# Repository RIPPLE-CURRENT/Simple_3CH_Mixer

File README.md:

# Simple_3CH_Mixer

Simple 3 Channel Eurorack synth Mixer

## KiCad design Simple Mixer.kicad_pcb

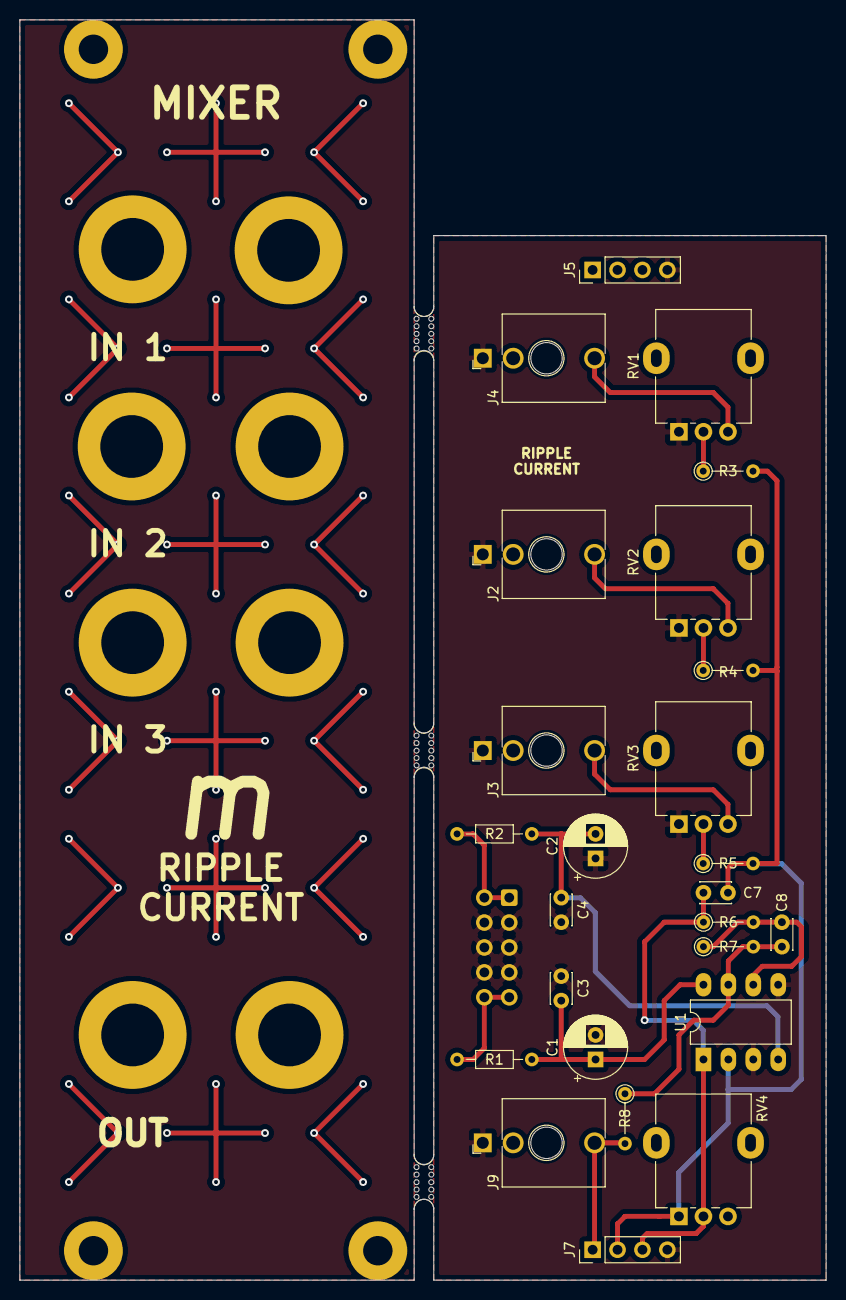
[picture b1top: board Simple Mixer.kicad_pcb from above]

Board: 2 copper layers, 82.2 x 128.5 mm, 29 parts (1 on the bottom side), 16 nets.

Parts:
C1, C2: 10u; CP_Radial_D6.3mm_P2.50mm
C3, C4: 100n; C_Disc_D3.0mm_W2.0mm_P2.50mm
C7, C8: 47pF; C_Disc_D3.0mm_W2.0mm_P2.50mm
J1: POWER INPUT; IDC-Header_2x05_P2.54mm_Vertical
J2: IN2; Jack_3.5mm_QingPu_WQP-PJ398SM_Vertical_CircularHoles
J3: IN3; Jack_3.5mm_QingPu_WQP-PJ398SM_Vertical_CircularHoles
J4: IN1; Jack_3.5mm_QingPu_WQP-PJ398SM_Vertical_CircularHoles
J5, J7: PCB JUMPER; PinHeader_1x04_P2.54mm_Vertical
J9: OUT; Jack_3.5mm_QingPu_WQP-PJ398SM_Vertical_CircularHoles
R1, R2: FERRITE; R_Axial_DIN0204_L3.6mm_D1.6mm_P7.62mm_Horizontal
R3, R4, R5, R6, R7: 100k; R_Axial_DIN0204_L3.6mm_D1.6mm_P5.08mm_Vertical
R8: 330; R_Axial_DIN0204_L3.6mm_D1.6mm_P5.08mm_Vertical
RV1, RV2, RV3, RV4: 100K; Potentiometer_Alpha_RD901F-40-00D_Single_Vertical
U1: TL072; DIP-8_W7.62mm_LongPads
mouse-bite-3mm-slot, mouse-bite-3mm-slot#2, mouse-bite-3mm-slot#3: VAL**; mouse-bite-3mm-slot

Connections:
+12V: C1.1, C3.2, R1.1, U1.8
-12V: C2.2, C4.1, R2.1, U1.4
GND: C1.2, C2.1, C3.1, C4.2, J1.3, J1.4, J1.5, J1.6, J1.7, J1.8, J2.G, J3.G, J4.G, J5.4, J7.4, J9.G, RV1.1, RV2.1, RV3.1, U1.3, U1.5
IN1: C7.2, J7.2, R3.2, R4.2, R5.2, RV4.1, U1.2
unnamed: C8.1, R7.2, R8.1, U1.7
unnamed: C8.2, R6.2, R7.1, U1.6
unnamed: J1.1, J1.2, R2.2
unnamed: J1.9, J1.10, R1.2
unnamed: J2.T, RV2.3
unnamed: J3.T, RV3.3
unnamed: J4.T, RV1.3
unnamed: R3.1, RV1.2
unnamed: R4.1, RV2.2
unnamed: R5.1, RV3.2
OUT: J7.1, J9.T, R8.2
VOL: C7.1, J7.3, R6.1, RV4.2, U1.1

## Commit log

2021-02-22 Set theme jekyll-theme-slate
